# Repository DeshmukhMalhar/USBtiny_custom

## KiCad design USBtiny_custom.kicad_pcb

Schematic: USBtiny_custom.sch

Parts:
C1, C2, C3: C_Small; C_0805_2012Metric_Pad1.15x1.40mm_HandSolder
C4: 100u/25V; CP_Elec_6.3x5.4_Nichicon
C5: 100u/25v; CP_Elec_6.3x5.4_Nichicon
C6, C7: 0u1; C_0805_2012Metric_Pad1.15x1.40mm_HandSolder
D1, D2: 3V6; D_MELF_Handsoldering
D3: SS34; D_SMA_Handsoldering
D4, D5: LED; LED_0805_2012Metric_Pad1.15x1.40mm_HandSolder
D6: 5v1/1W; D_MELF_Handsoldering
F1: Polyfuse_Small; R_1206_3216Metric_Pad1.42x1.75mm_HandSolder
J1: USB_B_Micro; USB_Micro-B
J2: USB_A; PinHeader_1x04_P2.54mm_Vertical
J3: AVR-ISP-6; PinHeader_2x03_P2.54mm_Vertical
R1: R_Small; R_0805_2012Metric_Pad1.15x1.40mm_HandSolder
R2, R3, R4: 100E; R_0805_2012Metric_Pad1.15x1.40mm_HandSolder
R5, R6: 510E; R_0805_2012Metric_Pad1.15x1.40mm_HandSolder
SW1: SW_SPDT; PinHeader_1x03_P2.54mm_Vertical
TP1: TestPoint_Flag; TestPoint_Pad_1.5x1.5mm
U1: ATtiny2313-20SU; SOIC-20W_7.5x12.8mm_P1.27mm
U2: 74125; SOIC-14_3.9x8.7mm_P1.27mm
Y1: 12M; Crystal_HC18-U_Vertical

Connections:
/B_EN: U1.8 (PD4|T0), U2.1 (E), U2.4 (E), U2.10 (E), U2.13 (E)
/D+: D2.1, J1.3, J2.3, R4.2
/D-: D1.1, J1.2, J2.2, R2.2, R3.1
/LED1: R6.1, U1.12 (PB0|AIN0|PC10)
/LED2: R5.1, U1.9 (PD5|OC0B|T1)
/MISO_p: U1.18 (PB6|MISO|PC16), U2.2 (D)
/MISO_t: J3.1, U2.3 (O)
/MOSI_p: U1.17 (PB5|MOSI|SDA|PC15), U2.11 (O)
/MOSI_t: J3.4, U2.12 (D)
/SCK_p: U1.19 (PB7|SCK|PC17), U2.5 (D)
/SCK_t: J3.3, U2.6 (O)
/~RST_p: U1.16 (PB4|OC1B|PC14), U2.9 (D)
/~RST_t: J3.5, U2.8 (O)
GND: C1.2, C2.2, C3.2, C4.2, C5.2, C6.2, C7.2, D1.2, D2.2, D4.1, D5.1, D6.2, J1.5, J1.6, J2.4, J3.6, U1.10 (GND), U2.7 (GND)
unnamed: C1.1, U1.5 (PA0|XTAL1), Y1.2
unnamed: C3.1, U1.4 (PA1|XTAL2), Y1.1
unnamed: D3.2, J1.1, J2.1
unnamed: D4.2, R5.2
unnamed: D5.2, R6.2
unnamed: F1.2, J3.2
unnamed: R1.2, TP1.1, U1.1 (PA2|~RESET)
unnamed: R2.1, U1.7 (PD3|INT1)
unnamed: R3.2, U1.11 (PD6|ICP)
unnamed: R4.1, U1.6 (PD2|XCK|INT0)
VBUS: C2.1, C5.1, D3.1, R1.1, SW1.3, U1.20 (VCC)
VCC: C4.1, C7.1, D6.1, F1.1, SW1.1
VDD: C6.1, SW1.2, U2.14 (VCC)

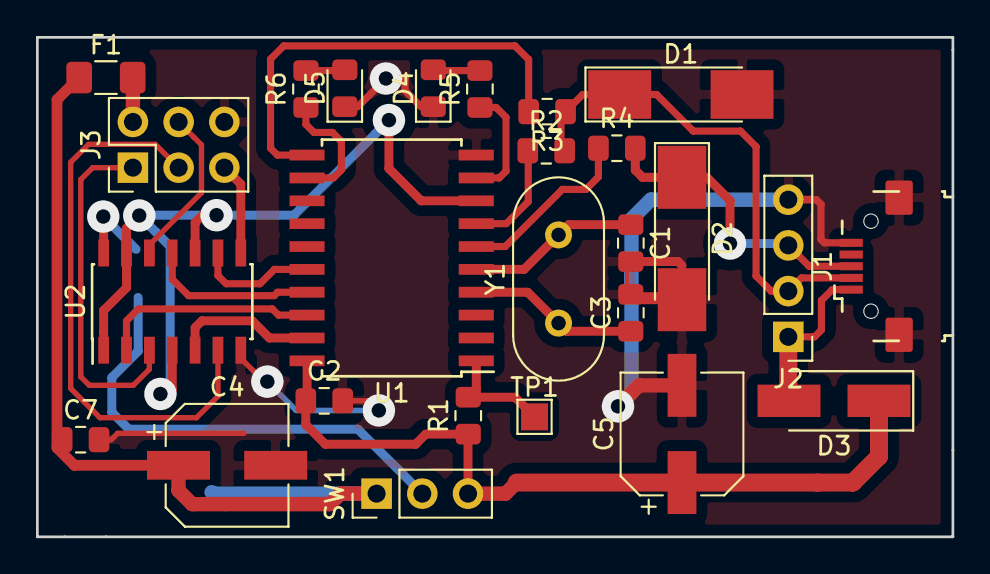
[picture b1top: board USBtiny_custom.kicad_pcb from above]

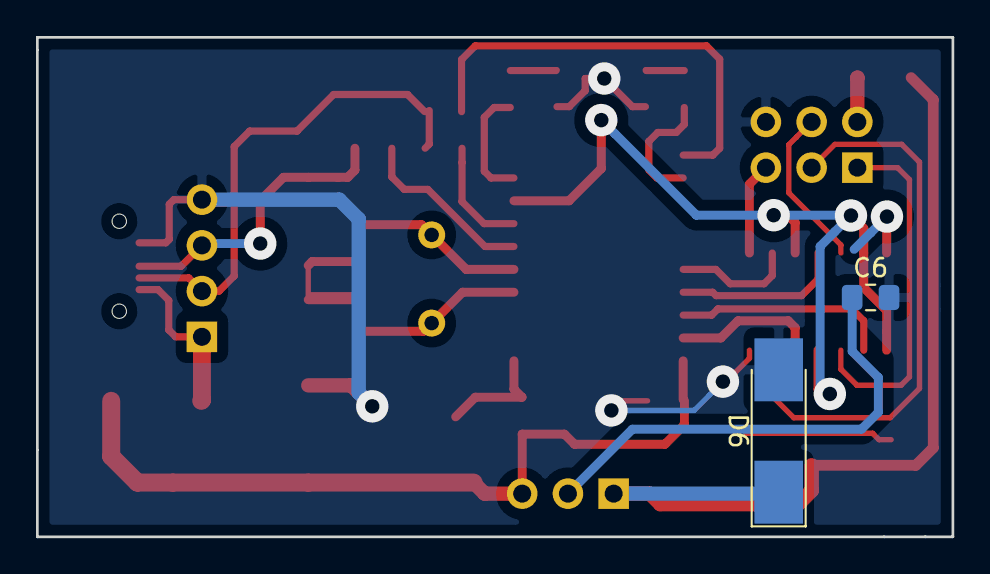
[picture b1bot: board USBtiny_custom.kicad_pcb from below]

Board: 2 copper layers, 50.9 x 27.7 mm, 28 parts (2 on the bottom side), 27 nets.

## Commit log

2019-01-21 Completed PCB
2019-05-20 add gitignore
2019-05-20 kicad meta update
